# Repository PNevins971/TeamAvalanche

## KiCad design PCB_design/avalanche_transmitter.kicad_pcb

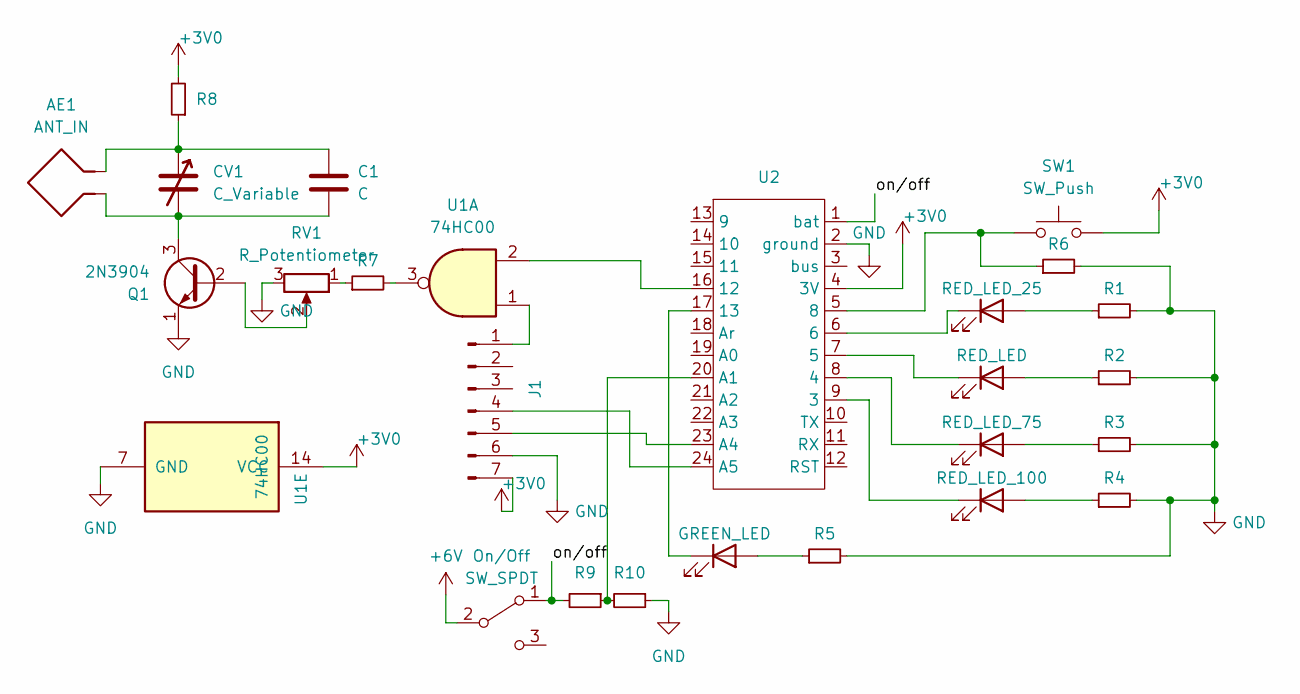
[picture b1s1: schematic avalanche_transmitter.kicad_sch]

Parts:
25%: RED_LED_100; LED_D5.0mm
50%: RED_LED_75; LED_D5.0mm
75%: RED_LED; LED_D5.0mm
100%: RED_LED_25; LED_D5.0mm
AE1: ANT_IN; PinHeader_1x02_P2.54mm_Vertical
C1: C; C_Disc_D4.7mm_W2.5mm_P5.00mm
CV1: C_Variable; C_Disc_D4.7mm_W2.5mm_P5.00mm
J1: Conn_01x07_Pin; PinHeader_1x07_P2.54mm_Vertical
On/Off: SW_SPDT; PinHeader_1x03_P2.54mm_Vertical
Q1: 2N3904; TO-92_Inline
R1, R2, R3, R4, R5, R6, R7, R8, R9, R10: R_Small; R_Axial_DIN0204_L3.6mm_D1.6mm_P7.62mm_Horizontal
RV1: R_Potentiometer; Potentiometer_Bourns_3296W_Vertical
SW1: SW_Push
TRANSMITTING: GREEN_LED; LED_D5.0mm
U1: 74HC00; DIP-14_W7.62mm
U2: pro_mini

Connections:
+3V0: J1.7, R8.2, SW1.2, U1.14 (VCC), U2.4 (3V)
+6V: On/Off.2 (B); also elsewhere on the board
/on/off: On/Off.1 (A), R9.2, U2.1 (bat)
GND: J1.6, Q1.1 (E), R1.2, R2.2, R3.2, R4.2, R5.2, R6.2, R10.1, RV1.3, U1.7 (GND), U2.2 (ground); also elsewhere on the board
unnamed: 75%.2 (A), R2.1
unnamed: 75%.1 (K), U2.7 (5)
unnamed: 50%.2 (A), R3.1
unnamed: 50%.1 (K), U2.8 (4)
unnamed: 25%.2 (A), R4.1
unnamed: 25%.1 (K), U2.9 (3)
unnamed: AE1.2, C1.1, CV1.1, R8.1
unnamed: 100%.2 (A), R1.1
unnamed: 100%.1 (K), U2.6
unnamed: J1.1, U1.1
unnamed: J1.4, U2.24 (A5)
unnamed: J1.5, U2.23 (A4)
unnamed: Q1.2 (B), RV1.2
unnamed: AE1.1, C1.2, CV1.2, Q1.3 (C)
unnamed: R7.1, RV1.1
unnamed: R7.2, U1.3
unnamed: R5.1, TRANSMITTING.2 (A)
unnamed: TRANSMITTING.1 (K), U2.17 (13)
unnamed: R6.1, SW1.1, U2.5 (8)
unnamed: U1.2, U2.16 (12)
unnamed: R9.1, R10.2, U2.20 (A1)

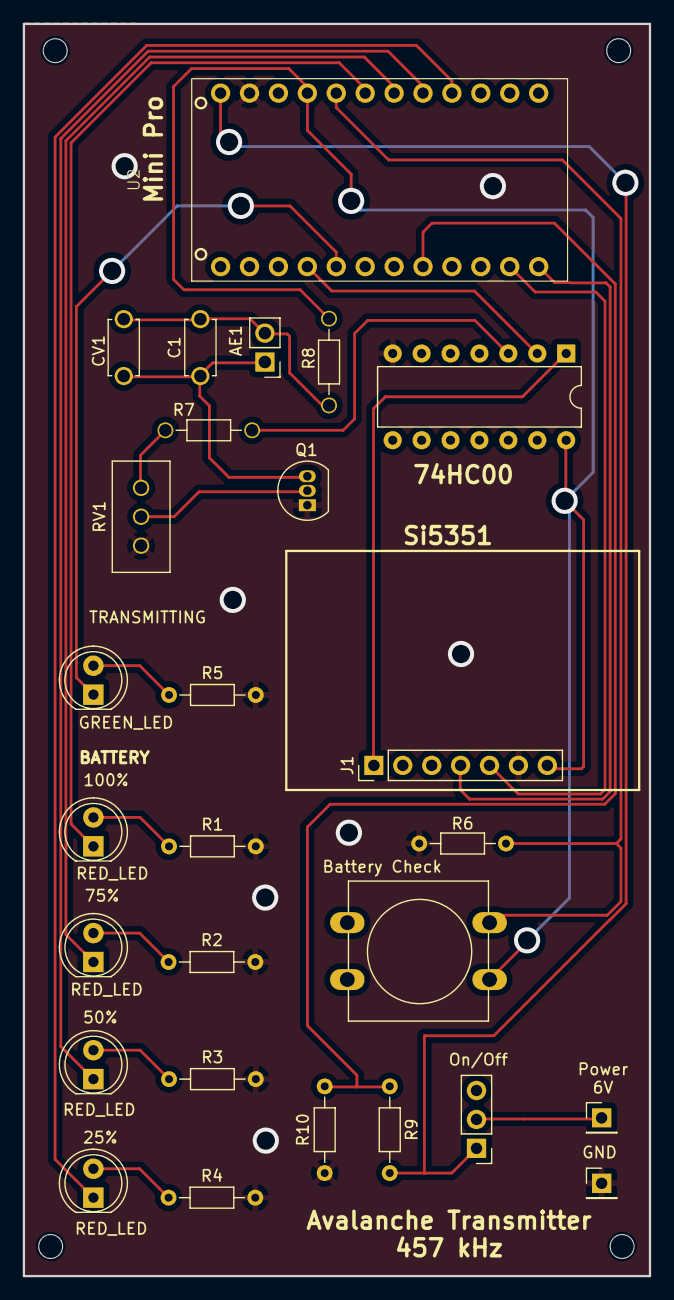
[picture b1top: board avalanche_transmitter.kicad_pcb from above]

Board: 2 copper layers, 55.0 x 110.0 mm, 26 parts (0 on the bottom side), 25 nets.

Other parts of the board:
Battery In (6V): PinHeader_1x01_P2.54mm_Vertical
GND: PinHeader_1x01_P2.54mm_Vertical

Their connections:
+6V: Battery In (6V).1; also elsewhere on the board
GND: GND.1; also elsewhere on the board

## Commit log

2024-01-12 Notes from ETSI EN 300 718-1 V1.2.1 (2001-05)
2024-01-25 Update LICENSE
2024-03-06 Clafer initial commit
2024-04-05 code to program IC via raspberry pi i2c
2024-04-07 pg21 and 22 are new
2024-04-07 code to initialize the si5351 at 457kHz
2024-04-09 Update si5351_init.ino
    tested on adafruit trinket
    and rasp pi pico
2024-04-09 Add files via upload
    code to produce the waveform on/off time specified by the standard
2024-04-16 Update arduinoTrinketCode_withDigitalSW.txt
    Removed adafruit si library only using etherkit library.
    Removed clockgen functions.
    Tested and functioning at freq and programmed duty cycle
2024-04-16 Updated Design Log
    Updated with 4/16 changes including images from scope of freq and duty cycle using transistor for switching
2024-04-16 Upload component datasheets
2024-04-28 test plan assignment
2024-05-15 PCB initial layout
2024-05-15 edited layout
2024-05-17 PCB updates
    Added some vias, rerouted some things, changed the footprint for the SI
2024-05-17 added series resistor to increase magfield
2024-05-18 finished PCB. ready for bens review
2024-05-18 updated layout. ready for review again
2024-05-22 adjusted pin connectors on PCB to lead to vias with red wires
2024-05-22 Changes ben recommended made
    added on/off switch
    added resistor in series with antenna
    swapped LEDs to correct direction
2024-05-22 QOL additions
    ready to print
2024-05-22 Added Battery Check Code and Green Tx Light
    Still needs code cleanup and comments
2024-05-22 Added voltage divider for battery check
2024-05-22 Manufacturing QOL updates
    Moved some traces
2024-05-26 Final PCB
2024-05-26 var cap pin hole size updated
2024-05-27 adjusted MCU footprint and hole diameter
2024-05-27 pcb finished
    pcb finished. gerber files and source uploaded
    receipt for oshpark print in folder
2024-06-11 comment and description cleanup
2024-06-11 Upload Circtui Fritzing Diagram
